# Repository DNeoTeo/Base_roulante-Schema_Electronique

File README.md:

# Base_roulante-Schema_Electronique

## Introduction

Dans le cadre du module Challenge, j’ai choisi de participer à la compétition de la coupe de France de Robotique 2023. Ce défi n’est pas envisageable tout seul. Avec des membres de l’association DTRE nous avons décidé de former une équipe. Ce « hackathon » nous a amené le défi de gérer et d’organiser une équipe de 29 personnes. À travers ce projet, j’ai pu travailler sur les différentes thématiques techniques telles que la programmation orienté objet, la mécanique ou encore l’électronique.

L’évènement a débuté le 10 septembre 2022 lors de la conférence de présentation de Planète Science organisé sur le campus d’EPITA. Ils y ont délivré la première version du règlement qui fut mis à jour quelques mois plus tard pour des questions d’homogénéités et pour clarifier certains points déséquilibré remontées par les équipes. Ce première évènement en début d’année nous a permis de poser toutes nos questions aux organisateurs et aux équipes vétéranes. Puisque nous sommes tous totalement novice de cette compétition. Le thème de cette année étant « The Cherry on the cake » pour fêter les 30 ans d’Eurobot, Planète Science demande aux équipes participant à la coupe de France de robotique de « cuisiner pour faire la fête ». 
Les missions fixées par le règlement de la 30ème édition sont : 

  − Fabriquer des gâteaux − Positionner la cerise sur les gâteaux   
  − Ranger le surplus des cerises dans le panier   
  − Se déguiser pour faire la fête. 
  
Sur le campus d’EPITA nous avons rencontré les organisateurs et des équipes habitués auprès desquelles nous avons pu prendre de précieux conseils.

Au début, Yasin, un membre de la DTRE et moi-même avons beaucoup travaillé en duo pour démarrer le projet puis nous avons délégué certaines parties aux membres qui ont rejoint l’équipe. J’ai ainsi participé à : 
  - Tous les entretiens des membres de l’équipe, 
  - La définition du budget (Annexe – Budget), 
  - La demande de subvention auprès de l’école ([Lien](https://docs.google.com/presentation/d/1tvP93IFA4L__9xUBjh1RfveQjmiez2jK/edit?usp=sharing&ouid=110299042600853966410&rtpof=true&sd=true)), 
  - Relecture du rapport PST de mi-année ([Lien](https://etesiea.sharepoint.com/:w:/r/sites/LesCavistes/Shared%20Documents/Rapport-PST/Rapport_PST_CDF_de_Robotique_2023.docx?d=w7245fce72372446c8502f77247498078&csf=1&web=1&e=gcsRpB)), 
  - Discussion avec les différents pôles pour connaître leur stratégie, 
  - Suivi de certains groupes pour s’assurer qu’ils n’avaient pas de problème à avancer, 
  - Récupération d’archive auprès d’une ancienne équipe ([Lien](https://etesiea.sharepoint.com/sites/LesCavistes/Shared%20Documents/Forms/AllItems.aspx?csf=1&web=1&e=nhDVeM&cid=38b68eae%2D38fa%2D46e4%2Db0cc%2D20c76cc6e8ef&RootFolder=%2Fsites%2FLesCavistes%2FShared%20Documents%2FGeneral%2FP%C3%B4les%2FBases%20roulante%2FArchives%20%2D%202012%20%2D%20Laval%20%2D%20RED&FolderCTID=0x012000E9F15A1BEC881E4E86D8D69B8AE829E8)) 
 
En plus de cette partie organisationnelle, je suis dans le pôle Base roulante spécialité électronique. J’ai ainsi réalisé plein de recherche pour le choix des composants de la base roulantes. 
Toutes les recherches sont dans le NoteBook suivant : [Elec – Base roulante](https://etesiea.sharepoint.com/:o:/r/sites/LesCavistes/_layouts/15/Doc.aspx?sourcedoc=%7B89e0934c-7b01-4295-8348-e438ad04fc94%7D&action=edit&wd=target(Notes%20de%20R%C3%A9union%2FElec%20-%20Notes%20de%20r%C3%A9unions.one%7Cb93d645d-10fc-47ad-a43a-4c280d625987%2FElec%20%E2%80%93%20Base%20roulante%7Cc344ee84-79c5-4be7-819a-d46dd6609212%2F)&wdorigin=703&wdpreservelink=1) ([Web view](https://etesiea.sharepoint.com/:o:/r/sites/LesCavistes/_layouts/15/Doc.aspx?sourcedoc=%7B89e0934c-7b01-4295-8348-e438ad04fc94%7D&action=edit&wd=target(Notes%20de%20R%C3%A9union%2FElec%20-%20Notes%20de%20r%C3%A9unions.one%7Cb93d645d-10fc-47ad-a43a-4c280d625987%2FElec%20%E2%80%93%20Base%20roulante%7Cc344ee84-79c5-4be7-819a-d46dd6609212%2F)&wdorigin=703&wdpreservelink=1)) Ce notebook est divisé en deux parties, à gauche la liste des composants adéquats pour toute la base roulante et ceux acheté pour le prototype n°1. Et à droite différentes parties théoriques et pistes de recherches pour bien choisir les composants. J’ai réalisé une chaîne fonctionnelle permet de visualiser l’ensemble de notre système : prise de décision avec la chaîne d’information, distribution de l’alimentation avec la chaîne d’énergie. On voit ainsi les composants nécessaires en fonction de leur rôle dans les 2 chaînes. Le diagramme électronique illustre la manière dont nos composants vont être reliés entre eux.

### La chaîne fonctionnelle

### Diagramme électrique

Premier prototype de la base roulante : https://drive.google.com/file/d/1hqDrjrIA7VDXRb-9ib1nsVt9VAf5gUXD/view?usp=share_link

En même que de mettre sur pieds, le prototype, j’ai commencé à faire les bibliothèques de composant sur eagle ainsi que les circuits imprimés. 

### Emergency_button (Board, Schematics et Librairy)

### Entrainement sur EAGLE

J’ai ainsi appris à créer des PCBs sur EAGLE avec la création de librairies ce qui inclut la création de schématics et de boards. Cette entrainement m’a permis de me familiariser avec les librairies de composants et l’IDE d’EAGLE.

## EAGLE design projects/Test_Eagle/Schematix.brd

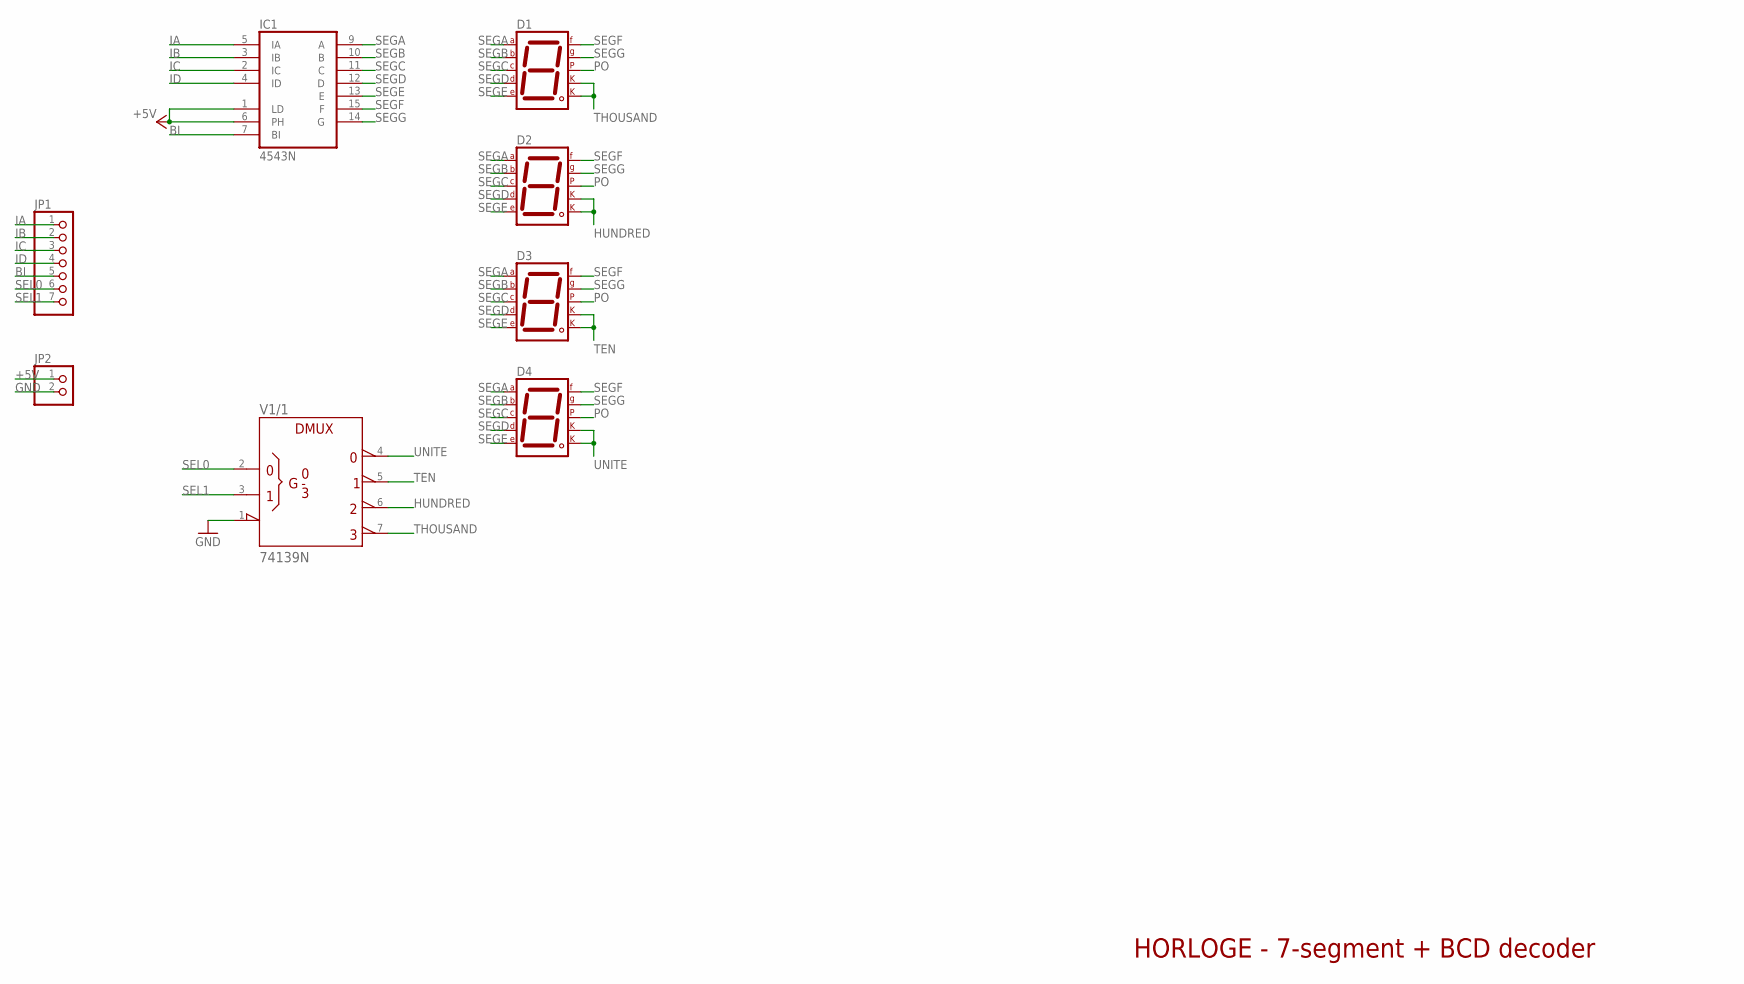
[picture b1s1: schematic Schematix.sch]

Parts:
D1, D2, D3, D4: 7SEG-CK; 7SEG-13
IC1: 4543N; DIL16
JP1: PINHD-1X7/90; 1X07/90
JP2: PINHD-1X2/90; 1X02/90
V1: 74139N; DIL16

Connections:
+5V: IC1.1 (LD), IC1.6 (PH), JP2.1
+UB: V1.16 (+UB)
-UB: V1.8 (-UB)
BI: IC1.7 (BI), JP1.5
GND: JP2.2, V1.1 (!G)
HUNDRED: D2.3 (CK1), D2.8 (CK2), V1.6 (Y2)
IA: IC1.5 (IA), JP1.1
IB: IC1.3 (IB), JP1.2
IC: IC1.2 (IC), JP1.3
ID: IC1.4 (ID), JP1.4
PO: D1.5 (DP), D2.5 (DP), D3.5 (DP), D4.5 (DP)
SEGA: D1.7 (A), D2.7 (A), D3.7 (A), D4.7 (A), IC1.9 (A)
SEGB: D1.6 (B), D2.6 (B), D3.6 (B), D4.6 (B), IC1.10 (B)
SEGC: D1.4 (C), D2.4 (C), D3.4 (C), D4.4 (C), IC1.11 (C)
SEGD: D1.2 (D), D2.2 (D), D3.2 (D), D4.2 (D), IC1.12 (D)
SEGE: D1.1 (E), D2.1 (E), D3.1 (E), D4.1 (E), IC1.13 (E)
SEGF: D1.9 (F), D2.9 (F), D3.9 (F), D4.9 (F), IC1.15 (F)
SEGG: D1.10 (G), D2.10 (G), D3.10 (G), D4.10 (G), IC1.14 (G)
SEL0: JP1.6, V1.2 (A)
SEL1: JP1.7, V1.3 (B)
TEN: D3.3 (CK1), D3.8 (CK2), V1.5 (Y1)
THOUSAND: D1.3 (CK1), D1.8 (CK2), V1.7 (Y3)
UNITE: D4.3 (CK1), D4.8 (CK2), V1.4 (Y0)
VDD: IC1.16 (VDD)
VSS: IC1.8 (VSS)

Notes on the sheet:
HORLOGE - 7-segment + BCD decoder

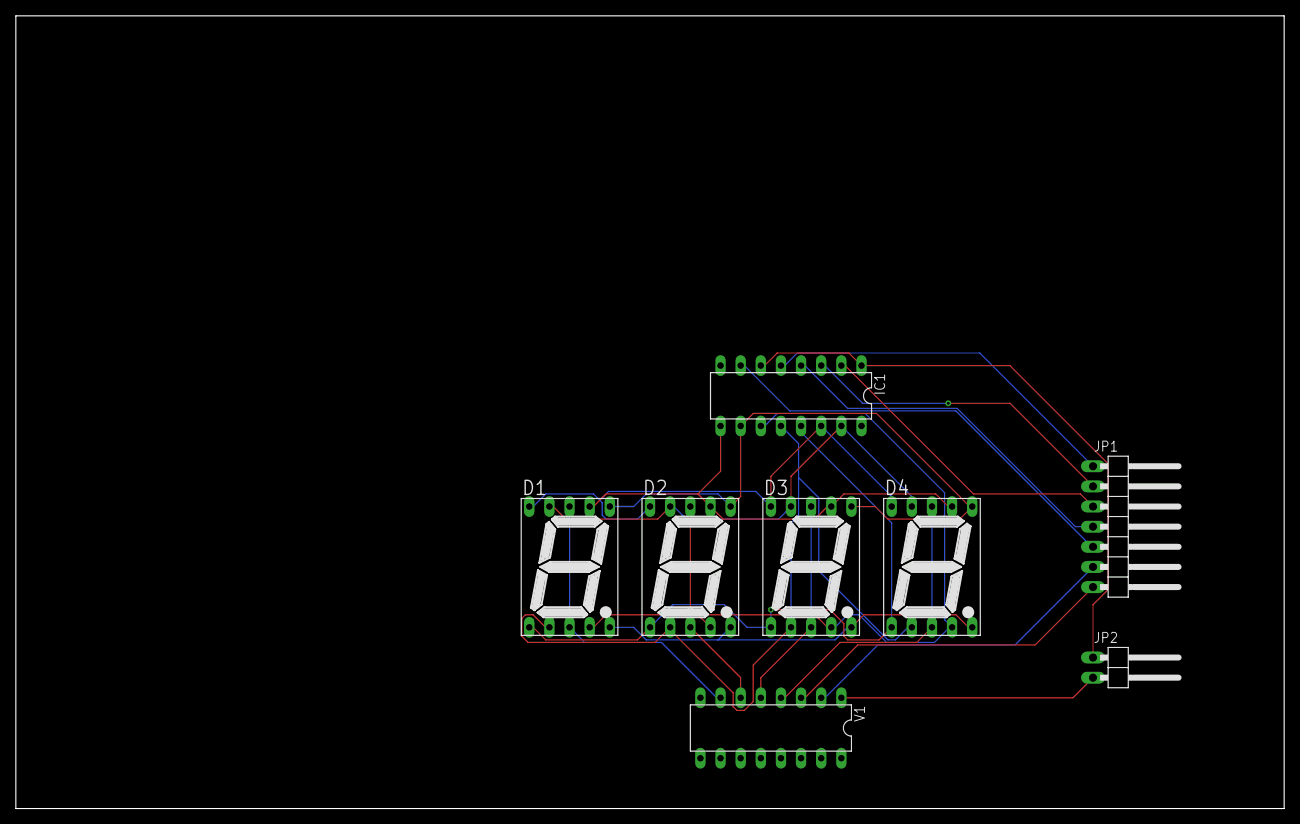
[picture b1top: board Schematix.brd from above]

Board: 2 copper layers, 160.0 x 100.0 mm, 8 parts (0 on the bottom side), 21 nets.

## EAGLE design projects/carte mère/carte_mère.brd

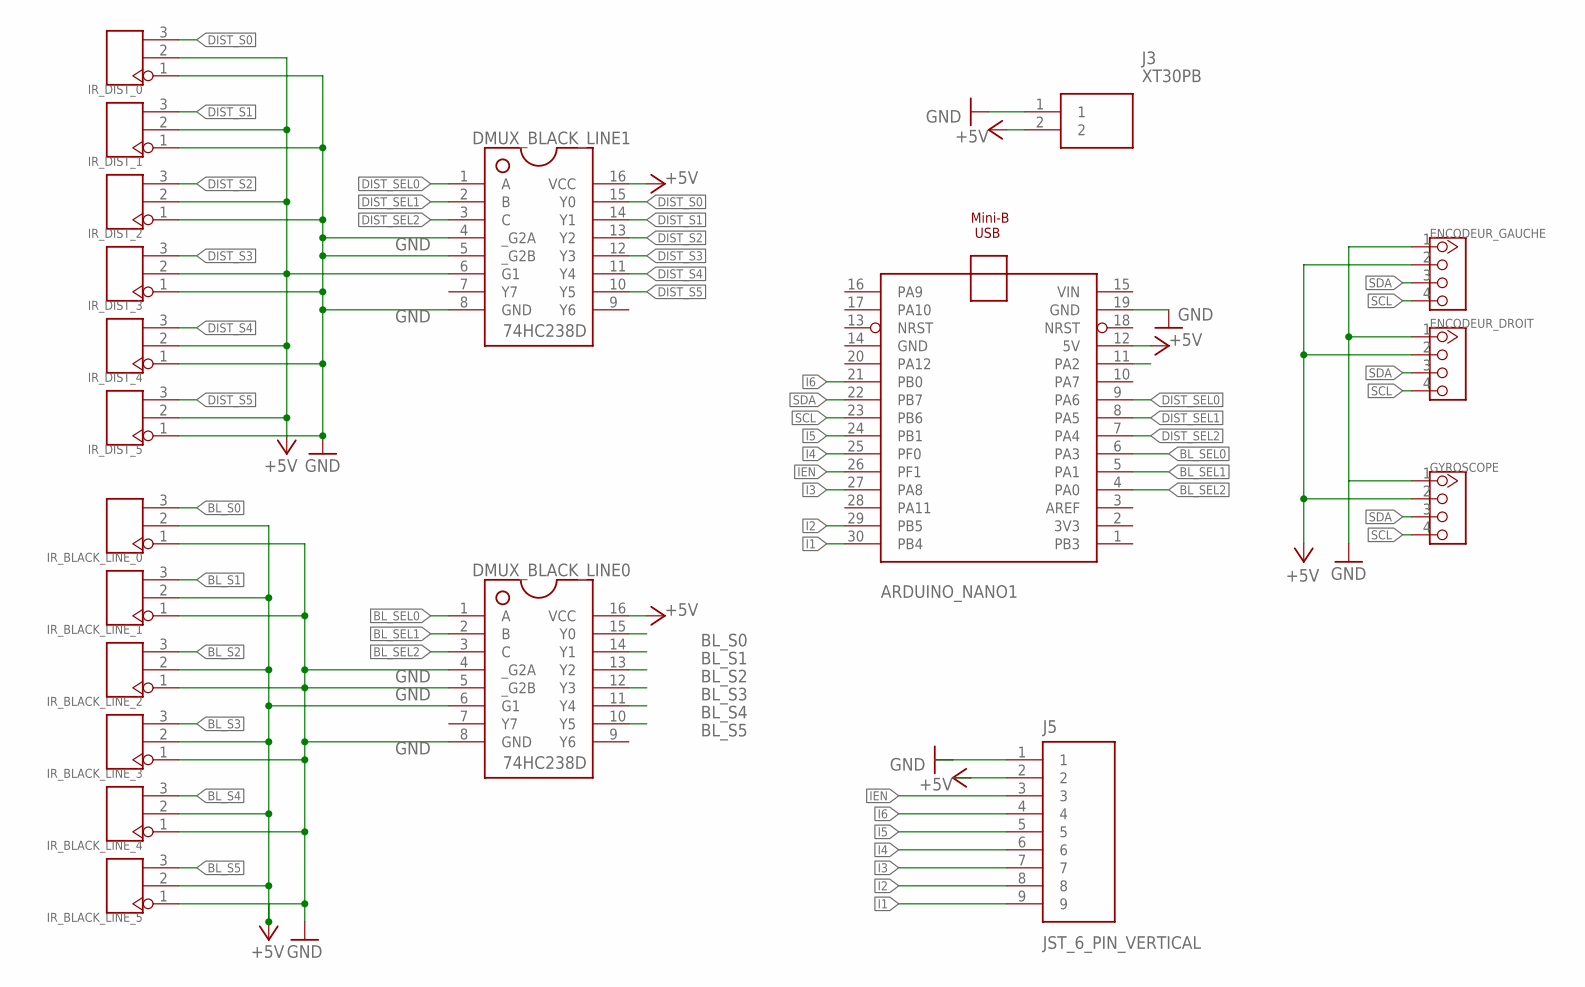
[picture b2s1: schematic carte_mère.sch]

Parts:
ARDUINO_NANO1: NUCLEO_F303K8
DMUX_BLACK_LINE0, DMUX_BLACK_LINE1: 74HC238D; SOIC127P600X175-16N
ENCODEUR_DROIT: TWIG-4P-2.0'90D'; 4P-2.0-90D
ENCODEUR_GAUCHE: TWIG-4P-2.0'90D'; 4P-2.0-90D
GYROSCOPE: TWIG-4P-2.0'90D'; 4P-2.0-90D
IR_BLACK_LINE_0, IR_BLACK_LINE_1, IR_BLACK_LINE_2, IR_BLACK_LINE_3, IR_BLACK_LINE_4, IR_BLACK_LINE_5: HEADER-3P-2.54; 3P-2.54
IR_DIST_0, IR_DIST_1, IR_DIST_2, IR_DIST_3, IR_DIST_4, IR_DIST_5: HEADER-3P-2.54; 3P-2.54
J3: XT30PB
J5: JST_6_PIN_VERTICAL; JST-6-SMD-VERT-1.0MM

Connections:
+5V: ARDUINO_NANO1.12 (5V), DMUX_BLACK_LINE0.6 (G1), DMUX_BLACK_LINE0.16 (VCC), DMUX_BLACK_LINE1.6 (G1), DMUX_BLACK_LINE1.16 (VCC), ENCODEUR_DROIT.2, ENCODEUR_GAUCHE.2, GYROSCOPE.2, IR_BLACK_LINE_0.2, IR_BLACK_LINE_1.2, IR_BLACK_LINE_2.2, IR_BLACK_LINE_3.2, IR_BLACK_LINE_4.2, IR_BLACK_LINE_5.2, IR_DIST_0.2, IR_DIST_1.2, IR_DIST_2.2, IR_DIST_3.2, IR_DIST_4.2, IR_DIST_5.2, J3.2, J5.2
BL_S0: DMUX_BLACK_LINE0.15 (Y0), IR_BLACK_LINE_0.3
BL_S1: DMUX_BLACK_LINE0.14 (Y1), IR_BLACK_LINE_1.3
BL_S2: DMUX_BLACK_LINE0.13 (Y2), IR_BLACK_LINE_2.3
BL_S3: DMUX_BLACK_LINE0.12 (Y3), IR_BLACK_LINE_3.3
BL_S4: DMUX_BLACK_LINE0.11 (Y4), IR_BLACK_LINE_4.3
BL_S5: DMUX_BLACK_LINE0.10 (Y5), IR_BLACK_LINE_5.3
BL_SEL0: ARDUINO_NANO1.6 (PA3), DMUX_BLACK_LINE0.1 (A)
BL_SEL1: ARDUINO_NANO1.5 (PA1), DMUX_BLACK_LINE0.2 (B)
BL_SEL2: ARDUINO_NANO1.4 (PA0), DMUX_BLACK_LINE0.3 (C)
DIST_S0: DMUX_BLACK_LINE1.15 (Y0), IR_DIST_0.3
DIST_S1: DMUX_BLACK_LINE1.14 (Y1), IR_DIST_1.3
DIST_S2: DMUX_BLACK_LINE1.13 (Y2), IR_DIST_2.3
DIST_S3: DMUX_BLACK_LINE1.12 (Y3), IR_DIST_3.3
DIST_S4: DMUX_BLACK_LINE1.11 (Y4), IR_DIST_4.3
DIST_S5: DMUX_BLACK_LINE1.10 (Y5), IR_DIST_5.3
DIST_SEL0: ARDUINO_NANO1.9 (PA6), DMUX_BLACK_LINE1.1 (A)
DIST_SEL1: ARDUINO_NANO1.8 (PA5), DMUX_BLACK_LINE1.2 (B)
DIST_SEL2: ARDUINO_NANO1.7 (PA4), DMUX_BLACK_LINE1.3 (C)
GND: ARDUINO_NANO1.14 (GND), ARDUINO_NANO1.19 (GND), DMUX_BLACK_LINE0.4 (_G2A), DMUX_BLACK_LINE0.5 (_G2B), DMUX_BLACK_LINE0.8 (GND), DMUX_BLACK_LINE1.4 (_G2A), DMUX_BLACK_LINE1.5 (_G2B), DMUX_BLACK_LINE1.8 (GND), ENCODEUR_DROIT.1, ENCODEUR_GAUCHE.1, GYROSCOPE.1, IR_BLACK_LINE_0.1, IR_BLACK_LINE_1.1, IR_BLACK_LINE_2.1, IR_BLACK_LINE_3.1, IR_BLACK_LINE_4.1, IR_BLACK_LINE_5.1, IR_DIST_0.1, IR_DIST_1.1, IR_DIST_2.1, IR_DIST_3.1, IR_DIST_4.1, IR_DIST_5.1, J3.1, J5.1
I1: ARDUINO_NANO1.30 (PB4), J5.9
I2: ARDUINO_NANO1.29 (PB5), J5.8
I3: ARDUINO_NANO1.27 (PA8), J5.7
I4: ARDUINO_NANO1.25 (PF0), J5.6
I5: ARDUINO_NANO1.24 (PB1), J5.5
I6: ARDUINO_NANO1.21 (PB0), J5.4
IEN: ARDUINO_NANO1.26 (PF1), J5.3
SCL: ARDUINO_NANO1.23 (PB6), ENCODEUR_DROIT.4, ENCODEUR_GAUCHE.4, GYROSCOPE.4
SDA: ARDUINO_NANO1.22 (PB7), ENCODEUR_DROIT.3, ENCODEUR_GAUCHE.3, GYROSCOPE.3
VIN: ARDUINO_NANO1.15 (VIN)

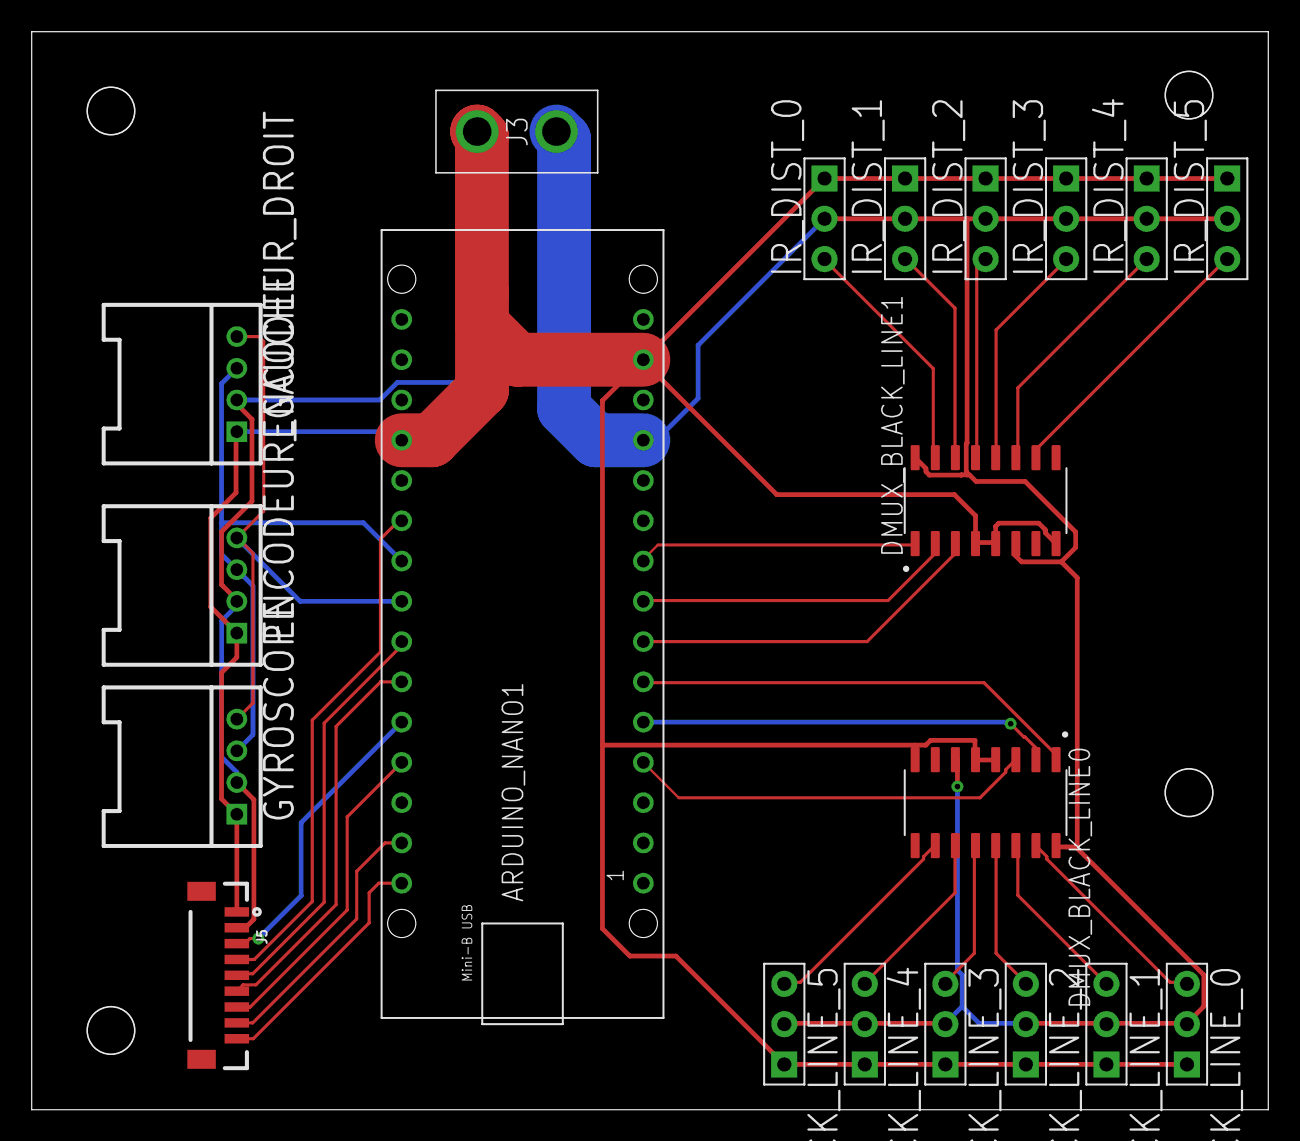
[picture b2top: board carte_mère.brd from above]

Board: 2 copper layers, 78.0 x 68.0 mm, 20 parts (0 on the bottom side), 29 nets.

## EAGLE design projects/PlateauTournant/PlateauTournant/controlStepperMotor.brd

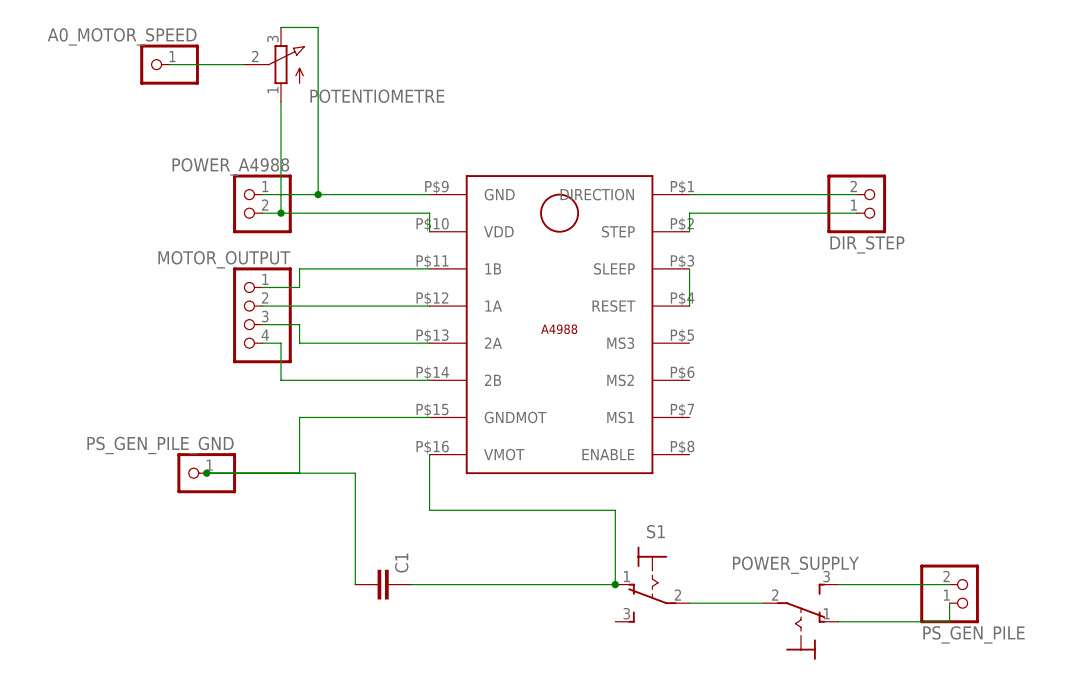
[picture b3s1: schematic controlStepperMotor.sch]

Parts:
A0_MOTOR_SPEED: PINHD-1X1; 1X01
C1: C2,5-3; C2.5-3
DIR_STEP: PINHD-1X2; 1X02
MOTOR_OUTPUT: PINHD-1X4; 1X04
POTENTIOMETRE: 3RP/1610N
POWER_A4988: PINHD-1X2; 1X02
POWER_SUPPLY: 320-916
PS_GEN_PILE: PINHD-1X2; 1X02
PS_GEN_PILE_GND: PINHD-1X1; 1X01
S1: M9040P
U$1: A4988-DRIVER-MOTOR

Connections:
unnamed: DIR_STEP.2, U$1.P$1 (DIRECTION)
unnamed: DIR_STEP.1, U$1.P$2 (STEP)
unnamed: POTENTIOMETRE.3 (E), POWER_A4988.1, U$1.P$9 (GND)
unnamed: POTENTIOMETRE.1 (A), POWER_A4988.2, U$1.P$10 (VDD)
unnamed: MOTOR_OUTPUT.1, U$1.P$11 (1B)
unnamed: MOTOR_OUTPUT.2, U$1.P$12 (1A)
unnamed: MOTOR_OUTPUT.3, U$1.P$13 (2A)
unnamed: MOTOR_OUTPUT.4, U$1.P$14 (2B)
unnamed: POWER_SUPPLY.2, S1.2
unnamed: C1.1, S1.1 (O), U$1.P$16 (VMOT)
unnamed: C1.2, PS_GEN_PILE_GND.1, U$1.P$15 (GNDMOT)
unnamed: POWER_SUPPLY.3 (S), PS_GEN_PILE.2
unnamed: POWER_SUPPLY.1 (O), PS_GEN_PILE.1
unnamed: A0_MOTOR_SPEED.1, POTENTIOMETRE.2 (S)

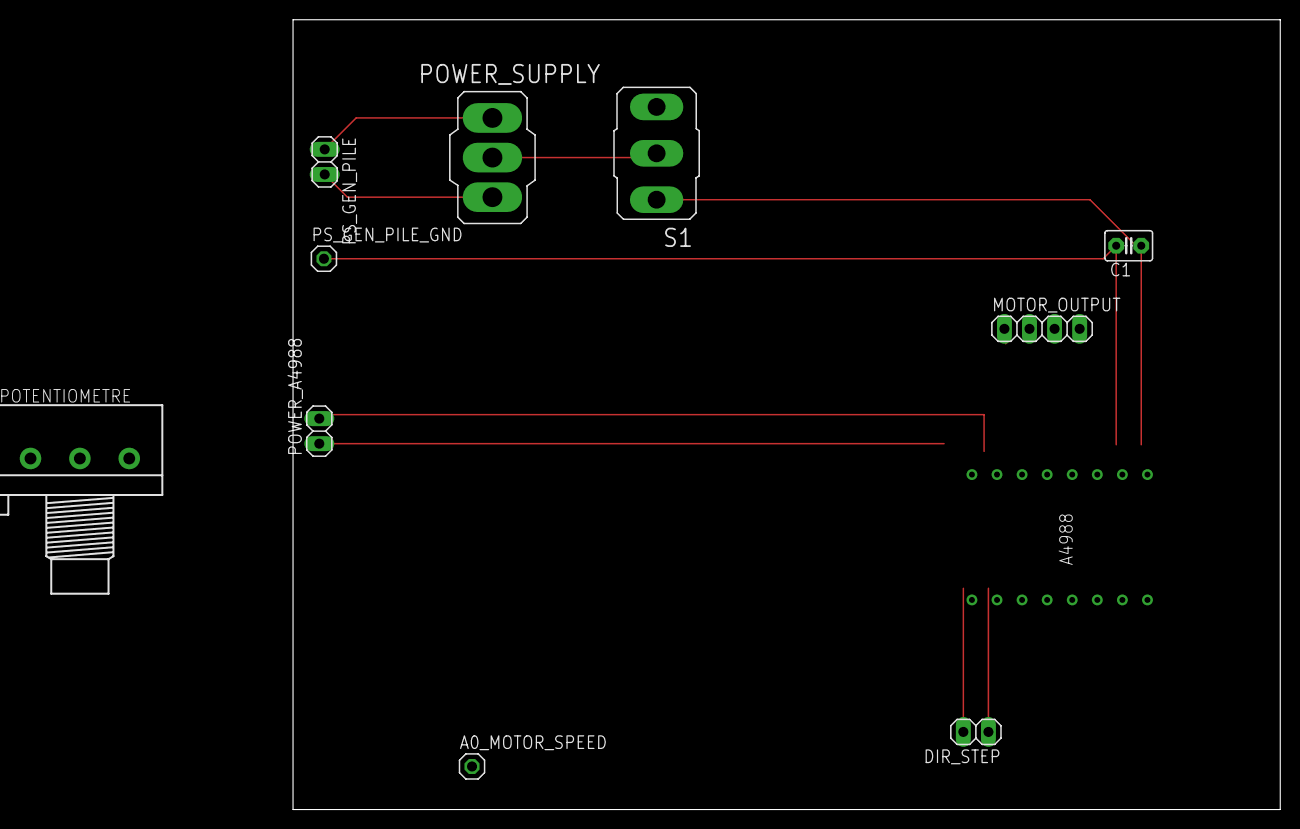
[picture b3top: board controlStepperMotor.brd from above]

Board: 2 copper layers, 100.0 x 80.0 mm, 11 parts (0 on the bottom side), 14 nets.

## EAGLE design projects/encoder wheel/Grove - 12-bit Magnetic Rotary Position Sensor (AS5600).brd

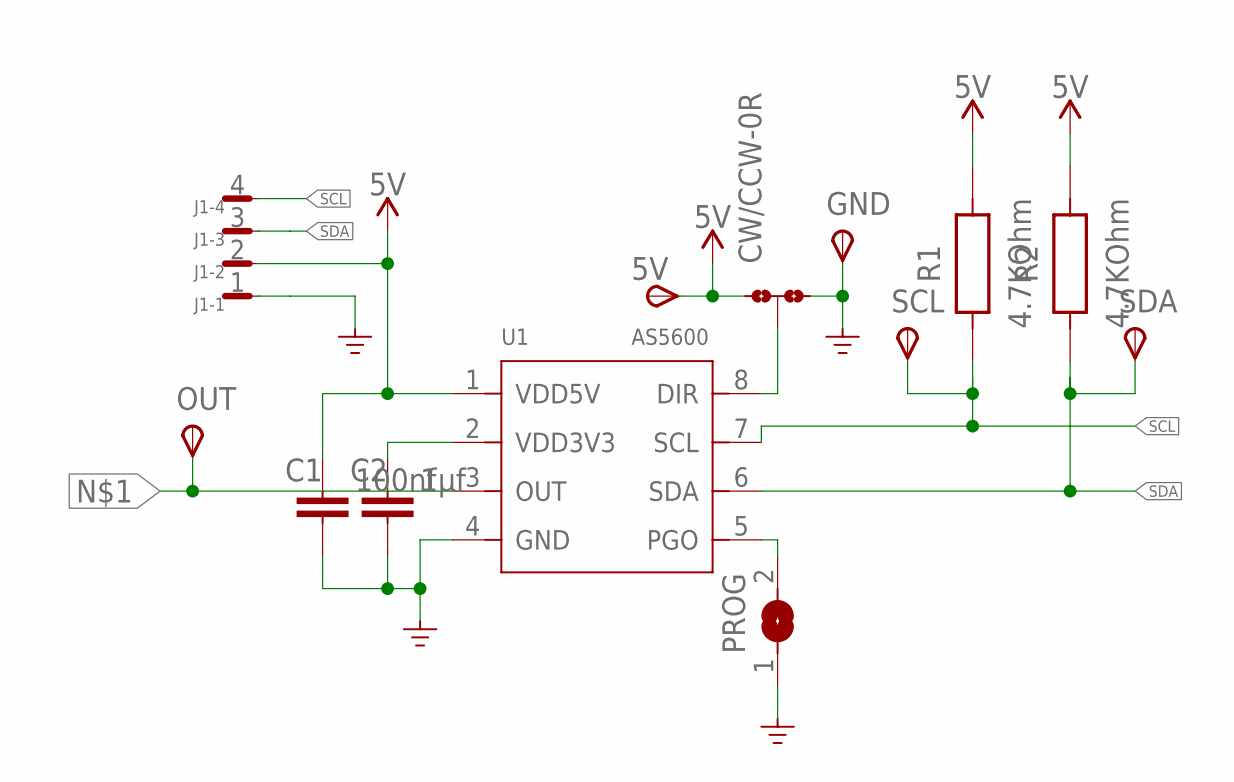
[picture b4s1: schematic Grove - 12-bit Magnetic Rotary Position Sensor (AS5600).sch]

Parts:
5V: TPSB2,54; B2,54
C1: 100nf; CAPC2012X110
C2: 1µf; CAPC2012X110
CW/CCW: 0R-JUMPA; A0R-JMP
GND: TPSB2,54; B2,54
J1: SM04B-SRSS-TB
OUT: TPSB2,54; B2,54
PROG: SJ
R1, R2: 4.7KOhm; WRIS-KSKE_0805_2.0X1.25X0.6(LXWXH)
SCL: TPSB2,54; B2,54
SDA: TPSB2,54; B2,54
U1: AS5600; SOIC8-1.27-5X4MM

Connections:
5V: 5V.TP, C1.1, CW/CCW.3, J1.2, R1.2, R2.2, U1.1 (VDD5V)
GND: C1.2, C2.2, CW/CCW.1, GND.TP, J1.1, PROG.1, U1.4 (GND)
unnamed: OUT.TP, U1.3 (OUT)
unnamed: CW/CCW.2, U1.8 (DIR)
unnamed: C2.1, U1.2 (VDD3V3)
unnamed: PROG.2, U1.5 (PGO)
SCL: J1.4, R1.1, SCL.TP, U1.7 (SCL)
SDA: J1.3, R2.1, SDA.TP, U1.6 (SDA)

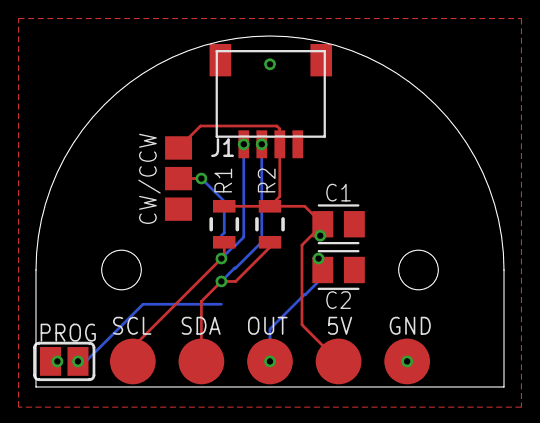
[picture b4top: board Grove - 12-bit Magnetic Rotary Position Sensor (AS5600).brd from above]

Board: 2 copper layers, 26.0 x 19.5 mm, 13 parts (1 on the bottom side), 8 nets.

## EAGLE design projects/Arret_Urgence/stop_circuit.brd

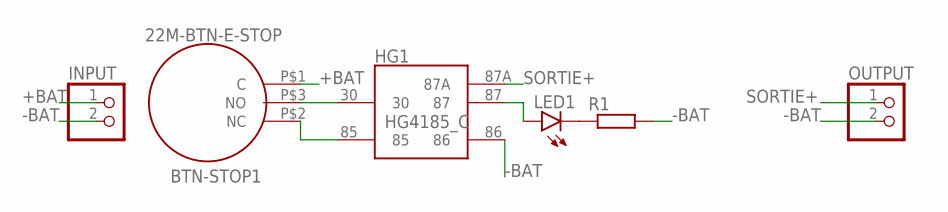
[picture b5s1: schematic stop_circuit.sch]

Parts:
BTN-STOP1: 22M-BTN-E-STOP; 22MM-BTN-E-STOP
HG1: HG4185_C; HG4185_C_1Z
INPUT: PINHD-1X2; 1X02
LED1: LEDB156; Q62902-B156
OUTPUT: PINHD-1X2; 1X02
R1: R-EU_0204/7; 0204/7

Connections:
+BAT: BTN-STOP1.P$1 (C), INPUT.1
-BAT: HG1.86, INPUT.2, OUTPUT.2, R1.2
unnamed: BTN-STOP1.P$3 (NO), HG1.30
unnamed: BTN-STOP1.P$2 (NC), HG1.85
unnamed: LED1.K (C), R1.1
unnamed: HG1.87, LED1.A
SORTIE+: HG1.87A, OUTPUT.1

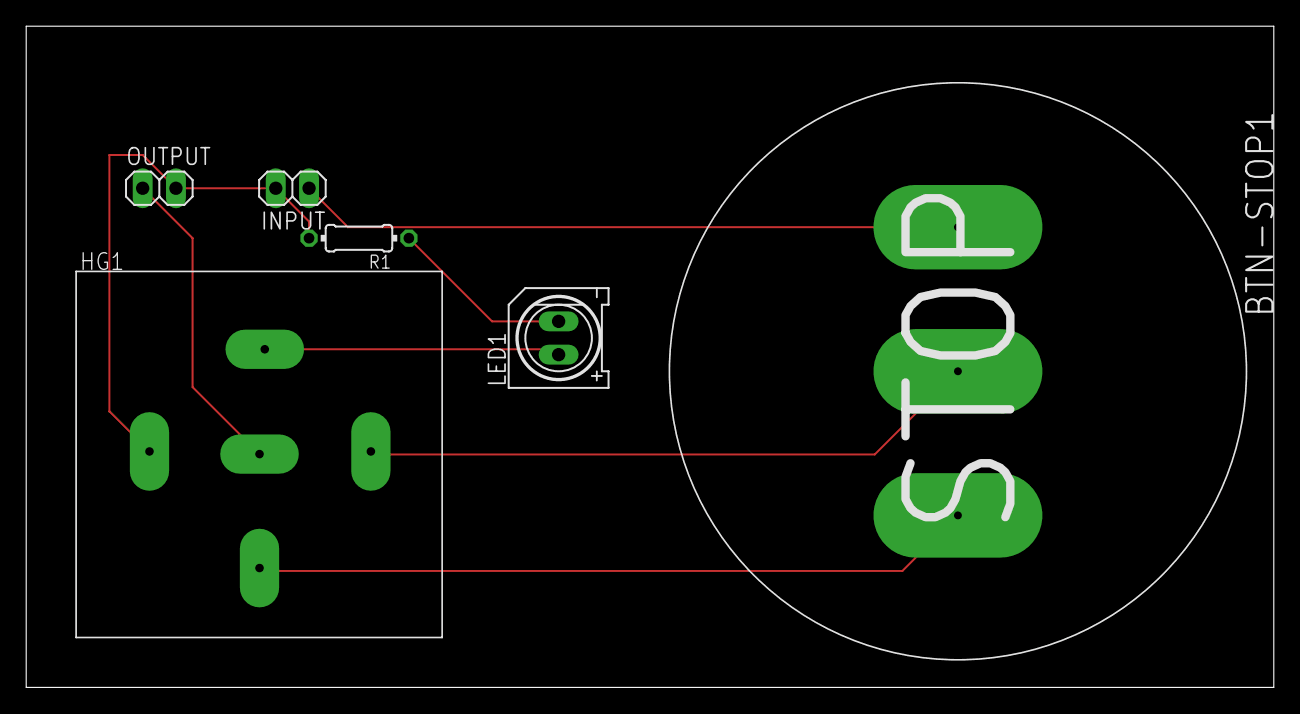
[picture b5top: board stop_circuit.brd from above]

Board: 2 copper layers, 95.2 x 50.5 mm, 6 parts (0 on the bottom side), 7 nets.

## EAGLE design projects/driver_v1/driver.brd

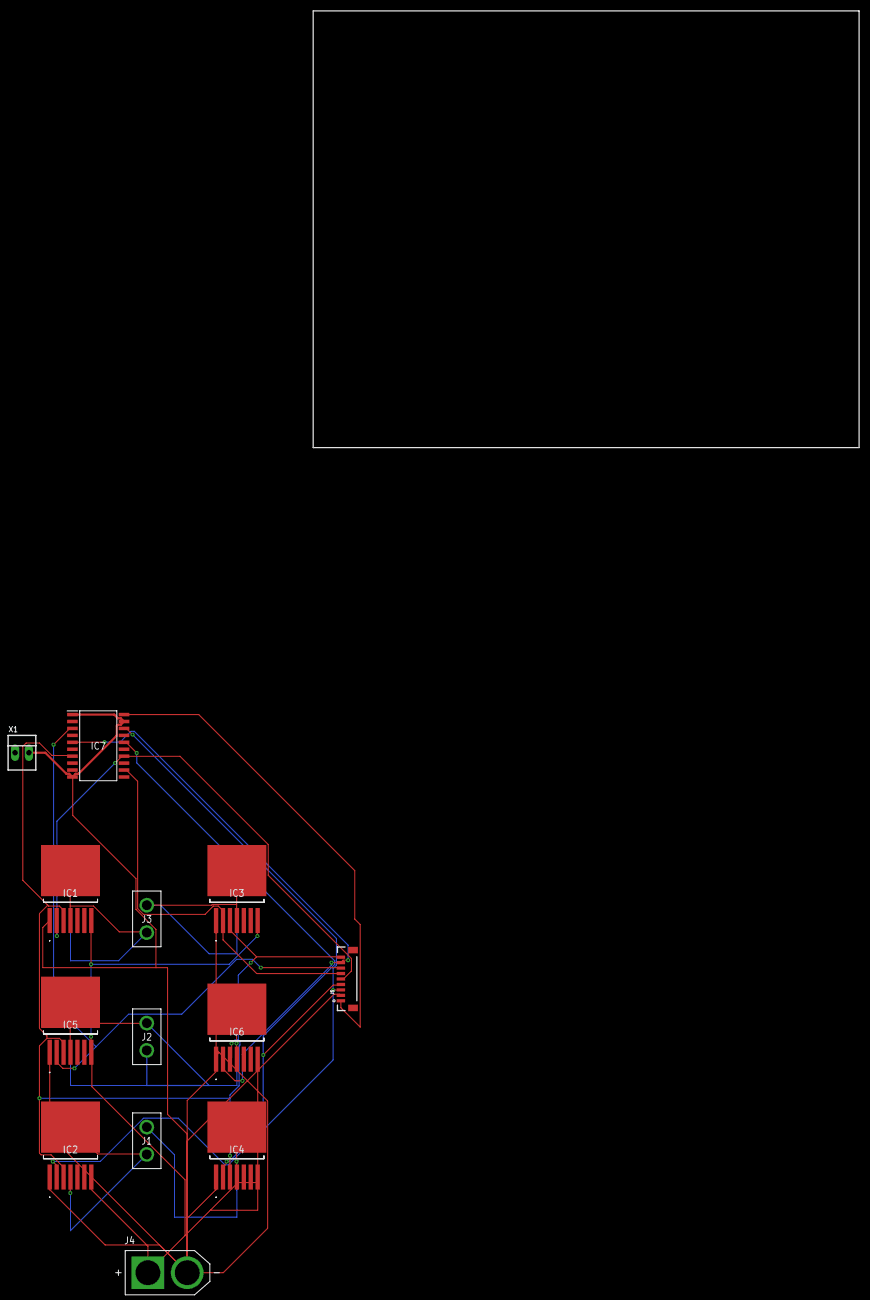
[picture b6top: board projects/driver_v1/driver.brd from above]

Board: 2 copper layers, 100.0 x 80.0 mm, 13 parts (0 on the bottom side), 16 nets.

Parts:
IC1, IC2, IC3, IC4, IC5, IC6: BTS7960B
IC7: SN74AHC244DW; SOIC127P1030X265-20N
J1, J2, J3: XT30PB
J4: XT60-M; AMASS_XT60-M
J5: JST_6_PIN_VERTICAL; JST-6-SMD-VERT-1.0MM
X1: 22-23-2021

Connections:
GND: IC1.1, IC2.1, IC3.1, IC4.1, IC5.1, IC6.1, IC7.1, IC7.10, IC7.19, J4.N, J5.2, X1.2
INH: IC1.3, IC2.3, IC3.3, IC4.3, IC5.3, IC6.3, IC7.7, J5.9
OUT1: IC2.4, IC2.8, J1.2
OUT2: IC4.4, IC4.8, J1.1
OUT3: IC6.4, IC6.8, J2.2
OUT4: IC5.4, IC5.8, J2.1
OUT5: IC3.4, IC3.8, J3.1
OUT6: IC1.4, IC1.8, J3.2
S1: IC2.2, IC7.18, J5.3
S2: IC4.2, IC7.16, J5.4
S3: IC1.2, IC7.14, J5.5
S4: IC3.2, IC7.12, J5.6
S5: IC5.2, IC7.3, J5.7
S6: IC6.2, IC7.5, J5.8
VCC: IC7.20, J5.1
VS: IC1.7, IC2.7, IC3.7, IC4.7, IC5.7, IC6.7, J4.P

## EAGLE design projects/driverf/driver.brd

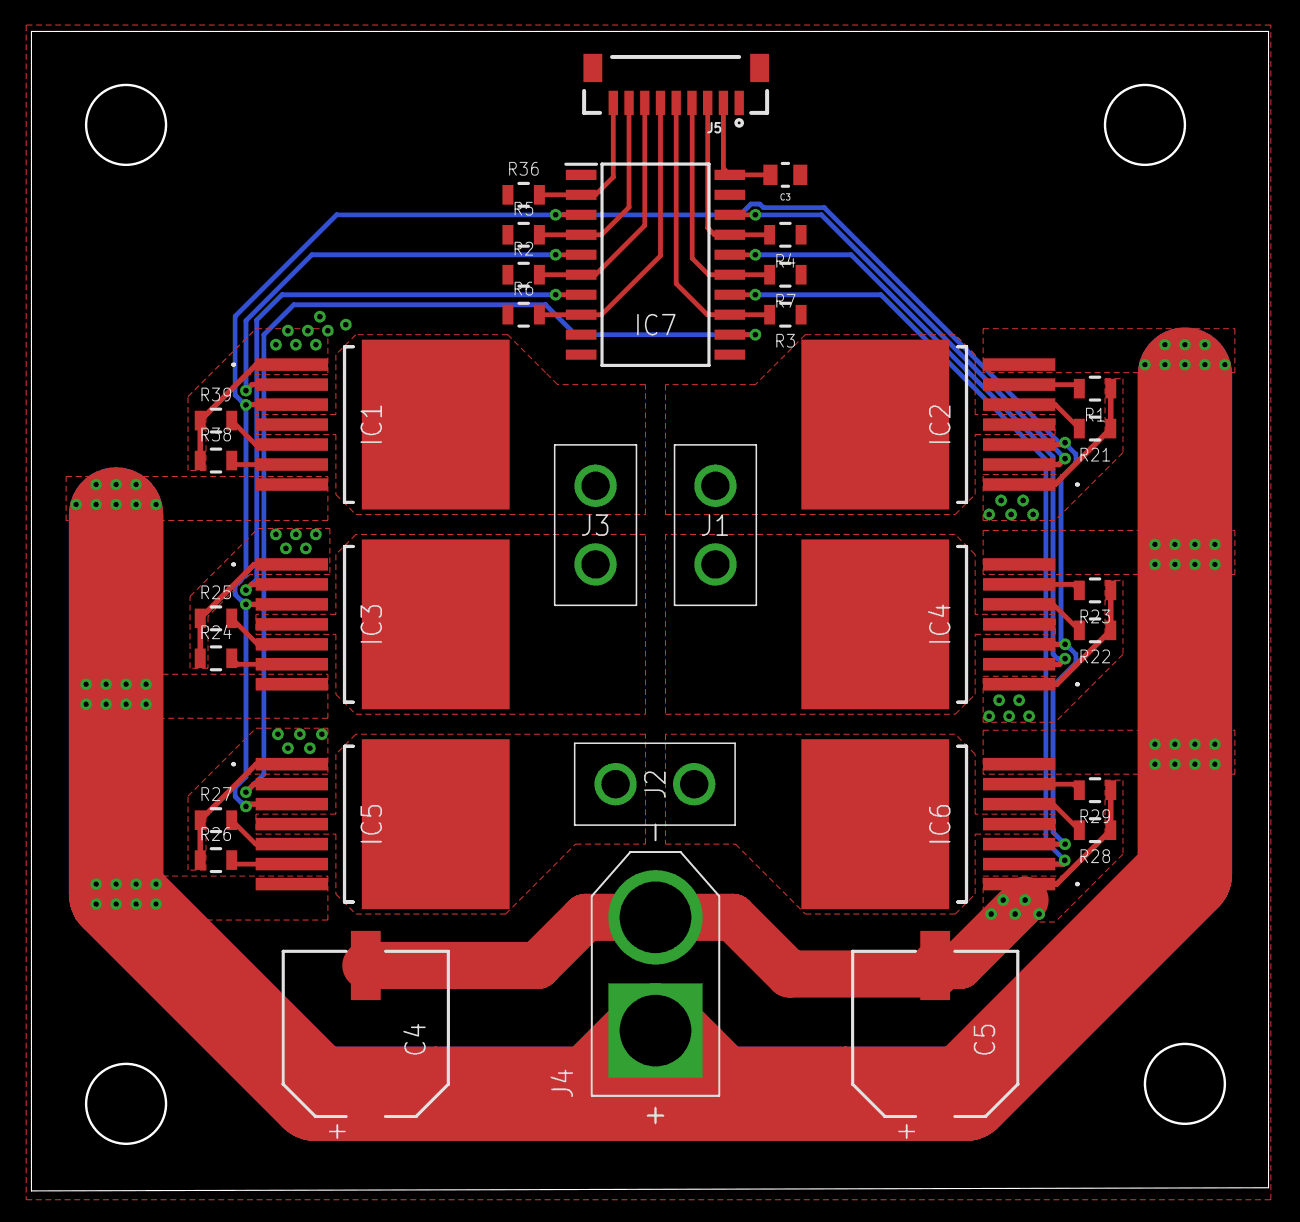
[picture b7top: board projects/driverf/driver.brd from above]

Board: 2 copper layers, 78.6 x 73.7 mm, 34 parts (0 on the bottom side), 35 nets.

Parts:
C3: 100nF; WCAP-CSST_0805
C4, C5: 330 µF; WCAP-AS5H_10X10.5(DXL)
IC1, IC2, IC3, IC4, IC5, IC6: BTS7960B
IC7: SN74AHC244DW; SOIC127P1030X265-20N
J1, J2, J3: XT30PB
J4: XT60-M; AMASS_XT60-M
J5: JST_6_PIN_VERTICAL; JST-6-SMD-VERT-1.0MM
R1, R2, R3, R4, R5, R6, R7, R21, R22, R23, R24, R25, R26, R27, R28, R29, R36, R38, R39: 10k; WRIS-KSKE_0805_2.0X1.25X0.6(LXWXH)

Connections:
GND: C3.1, C4.2, C5.2, IC1.1, IC2.1, IC3.1, IC4.1, IC5.1, IC6.1, IC7.1, IC7.10, IC7.11, IC7.19, J4.N, J5.1, R1.1, R2.1, R3.1, R4.1, R5.1, R6.1, R7.1, R21.1, R22.1, R23.1, R24.1, R25.1, R26.1, R27.1, R28.1, R29.1, R36.1, R38.1, R39.1
I1: IC7.2, J5.9, R36.2
I2: IC7.4, J5.8, R5.2
I3: IC7.6, J5.7, R2.2
I4: IC7.8, J5.6, R6.2
I5: IC7.13, J5.5, R3.2
I6: IC7.15, J5.4, R7.2
IEN: IC7.17, J5.3, R4.2
unnamed: IC2.6, R1.2
unnamed: IC1.6, R38.2
unnamed: IC1.5, R39.2
unnamed: IC2.5, R21.2
unnamed: IC3.6, R24.2
unnamed: IC3.5, R25.2
unnamed: IC4.6, R23.2
unnamed: IC4.5, R22.2
unnamed: IC5.6, R26.2
unnamed: IC5.5, R27.2
unnamed: IC6.6, R29.2
unnamed: IC6.5, R28.2
OUT1: IC2.4, IC2.8, J1.2
OUT2: IC4.4, IC4.8, J1.1
OUT3: IC6.4, IC6.8, J2.2
OUT4: IC5.4, IC5.8, J2.1
OUT5: IC3.4, IC3.8, J3.1
OUT6: IC1.4, IC1.8, J3.2
S1: IC2.2, IC7.18
S2: IC4.2, IC7.16
S3: IC6.2, IC7.14
S4: IC5.2, IC7.12
S5: IC3.2, IC7.7
S6: IC1.2, IC7.5
SEN: IC1.3, IC2.3, IC3.3, IC4.3, IC5.3, IC6.3, IC7.3
VCC: C3.2, IC7.20, J5.2
VS: C4.1, C5.1, IC1.7, IC2.7, IC3.7, IC4.7, IC5.7, IC6.7, J4.P

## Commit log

2023-03-08 New circuit
2023-05-22 Ajout des circuits imprimés EAGLE, d'entrainemet mais aussi les circuits finaux de la base roulante de la CDFR

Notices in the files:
parts and their libraries:
SparkFun-Connectors_JST_SH: Licensing: Creative Commons ShareAlike 4.0 International - https://creativecommons.org/licenses/by-sa/4.0
Wurth_Resistor_WRIS-KSKE: Copyright: Würth Elektronik
